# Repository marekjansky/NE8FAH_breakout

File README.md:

# NE8FAH_breakout
Breakout board for each pair of the ethercon connector

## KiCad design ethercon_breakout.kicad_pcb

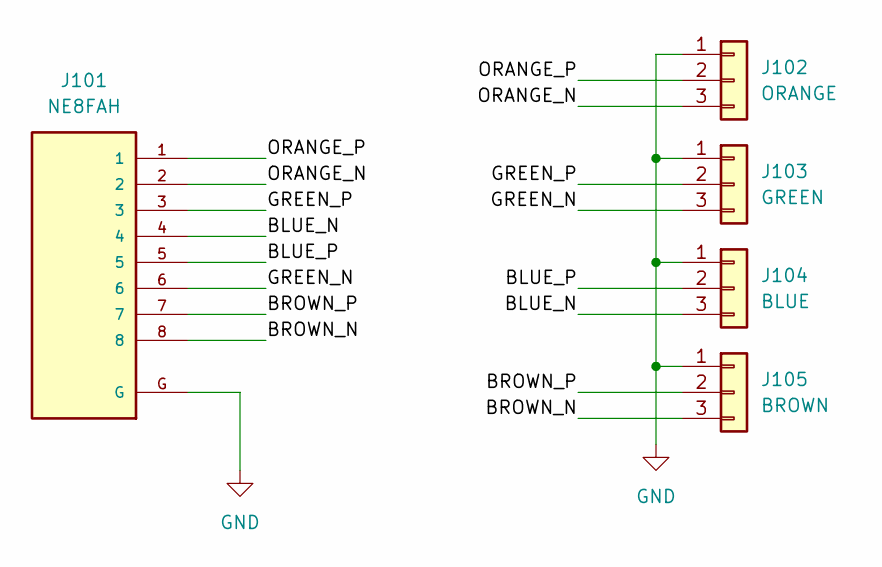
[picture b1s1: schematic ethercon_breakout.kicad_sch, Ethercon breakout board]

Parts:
J101: NE8FAH; NEUTRIK_NE8FAH; PARTREV 16.04.02
J102: ORANGE; PinHeader_1x03_P2.54mm_Vertical
J103: GREEN; PinHeader_1x03_P2.54mm_Vertical
J104: BLUE; PinHeader_1x03_P2.54mm_Vertical
J105: BROWN; PinHeader_1x03_P2.54mm_Vertical

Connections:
/BLUE_N: J101.4, J104.3
/BLUE_P: J101.5, J104.2
/BROWN_N: J101.8, J105.3
/BROWN_P: J101.7, J105.2
/GREEN_N: J101.6, J103.3
/GREEN_P: J101.3, J103.2
/ORANGE_N: J101.2, J102.3
/ORANGE_P: J101.1, J102.2
GND: J101.G, J102.1, J103.1, J104.1, J105.1

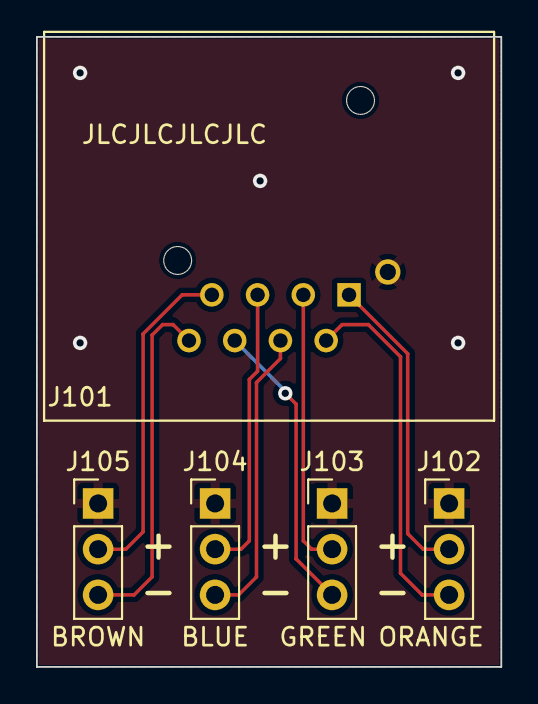
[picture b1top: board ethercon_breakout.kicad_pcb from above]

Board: 2 copper layers, 25.8 x 35.0 mm, 5 parts (0 on the bottom side), 9 nets.

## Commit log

2024-03-12 Edited gitignore
2024-03-12 Breakout first version
2024-03-12 Changed schematic title
2024-03-12 Add DRC exclusions for silkscreen
2024-03-25 Added origin to PCB
2024-03-26 Added FreeCAD enclosure
